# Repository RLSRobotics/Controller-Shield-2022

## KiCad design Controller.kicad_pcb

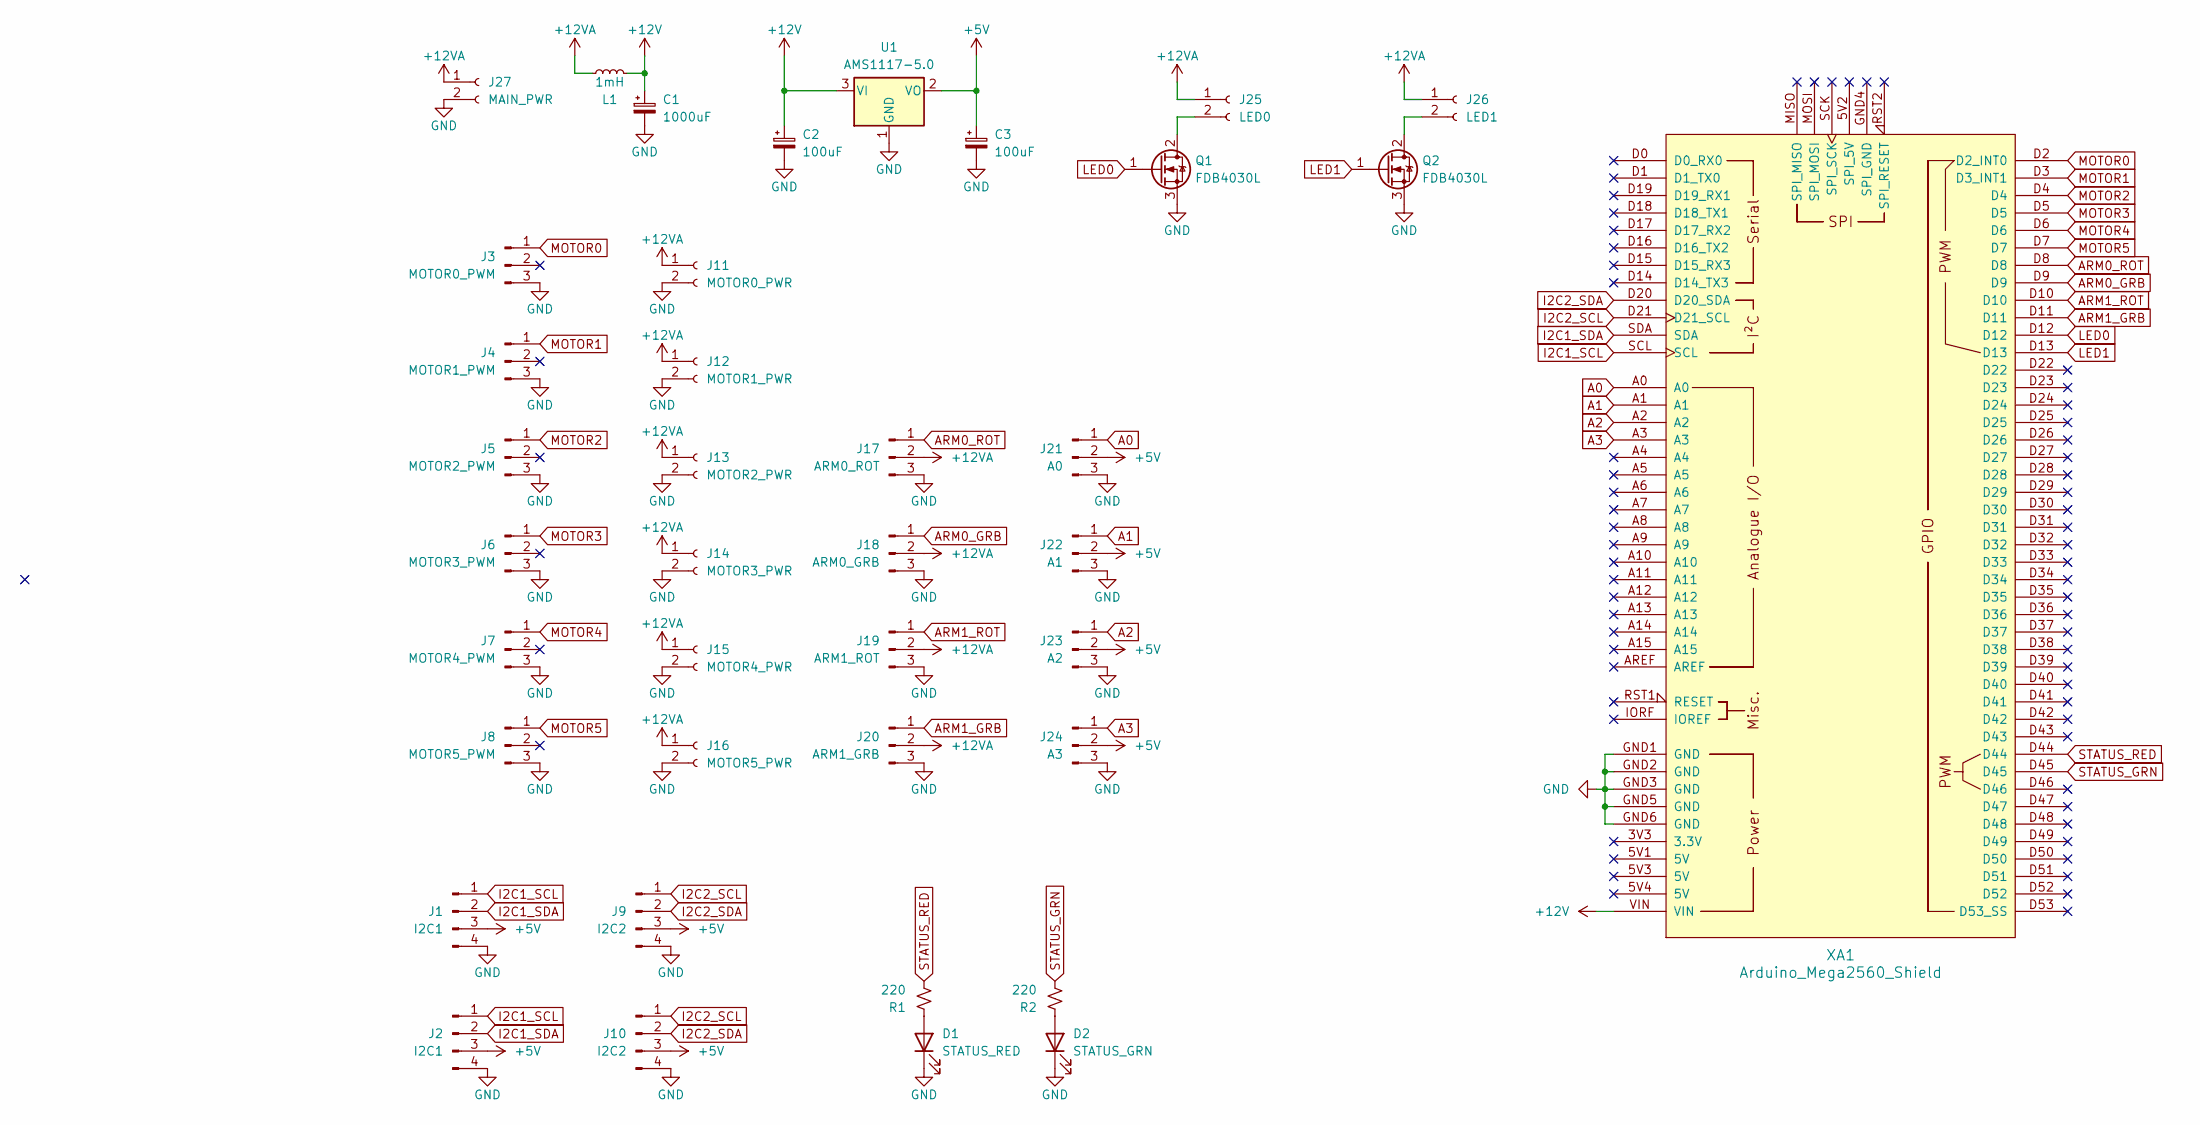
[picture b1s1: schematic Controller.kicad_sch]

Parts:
C1: 1000uF; CP_Radial_D12.5mm_P5.00mm; Part Number UVR1V102MHD
C2, C3: 100uF; CP_Elec_6.3x5.9; Part Number UCW1E101MCL1GS
D1: STATUS_RED; D_0603_1608Metric_Pad1.05x0.95mm_HandSolder
D2: STATUS_GRN; D_0603_1608Metric_Pad1.05x0.95mm_HandSolder
J1, J2: I2C1; PinHeader_1x04_P2.54mm_Horizontal
J3: MOTOR0_PWM; PinHeader_1x03_P2.54mm_Horizontal
J4: MOTOR1_PWM; PinHeader_1x03_P2.54mm_Horizontal
J5: MOTOR2_PWM; PinHeader_1x03_P2.54mm_Horizontal
J6: MOTOR3_PWM; PinHeader_1x03_P2.54mm_Horizontal
J7: MOTOR4_PWM; PinHeader_1x03_P2.54mm_Horizontal
J8: MOTOR5_PWM; PinHeader_1x03_P2.54mm_Horizontal
J9, J10: I2C2; PinHeader_1x04_P2.54mm_Horizontal
J11: MOTOR0_PWR; ESC-PWR
J12: MOTOR1_PWR; ESC-PWR
J13: MOTOR2_PWR; ESC-PWR
J14: MOTOR3_PWR; ESC-PWR
J15: MOTOR4_PWR; ESC-PWR
J16: MOTOR5_PWR; ESC-PWR
J17: ARM0_ROT; PinHeader_1x03_P2.54mm_Horizontal
J18: ARM0_GRB; PinHeader_1x03_P2.54mm_Horizontal
J19: ARM1_ROT; PinHeader_1x03_P2.54mm_Horizontal
J20: ARM1_GRB; PinHeader_1x03_P2.54mm_Horizontal
J21: A0; PinHeader_1x03_P2.54mm_Horizontal
J22: A1; PinHeader_1x03_P2.54mm_Horizontal
J23: A2; PinHeader_1x03_P2.54mm_Horizontal
J24: A3; PinHeader_1x03_P2.54mm_Horizontal
J25: LED0; TerminalBlock_bornier-2_P5.08mm
J26: LED1; TerminalBlock_bornier-2_P5.08mm
J27: MAIN_PWR; ESC-PWR
L1: 1mH; L_Radial_D24.4mm_P23.40mm_Murata_1400series; Part Number 1410516C
Q1, Q2: FDB4030L; TO-263-2
R1, R2: 220; R_0603_1608Metric_Pad0.98x0.95mm_HandSolder
U1: AMS1117-5.0; SOT-223-3_TabPin2
XA1: Arduino_Mega2560_Shield

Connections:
+5V: C3.1, J1.3, J2.3, J9.3, J10.3, J21.2, J22.2, J23.2, J24.2, U1.2 (VO)
+12V: C1.1, C2.1, L1.2, U1.3 (VI), XA1.VIN
+12VA: J11.1, J12.1, J13.1, J14.1, J15.1, J16.1, J17.2, J18.2, J19.2, J20.2, J25.1, J26.1, J27.1, L1.1
A0: J21.1, XA1.A0
A1: J22.1, XA1.A1
A2: J23.1, XA1.A2
A3: J24.1, XA1.A3
ARM0_GRB: J18.1, XA1.D9
ARM0_ROT: J17.1, XA1.D8
ARM1_GRB: J20.1, XA1.D11
ARM1_ROT: J19.1, XA1.D10
GND: C1.2, C2.2, C3.2, D1.1 (K), D2.1 (K), J1.4, J2.4, J3.3, J4.3, J5.3, J6.3, J7.3, J8.3, J9.4, J10.4, J11.2, J12.2, J13.2, J14.2, J15.2, J16.2, J17.3, J18.3, J19.3, J20.3, J21.3, J22.3, J23.3, J24.3, J27.2, Q1.3 (S), Q2.3 (S), U1.1 (GND), XA1.GND1 (GND), XA1.GND2 (GND), XA1.GND3 (GND), XA1.GND5 (GND), XA1.GND6 (GND)
I2C1_SCL: J1.1, J2.1, XA1.SCL
I2C1_SDA: J1.2, J2.2, XA1.SDA
I2C2_SCL: J9.1, J10.1, XA1.D21 (D21_SCL)
I2C2_SDA: J9.2, J10.2, XA1.D20 (D20_SDA)
LED0: Q1.1 (G), XA1.D12
LED1: Q2.1 (G), XA1.D13
MOTOR0: J3.1, XA1.D2 (D2_INT0)
MOTOR1: J4.1, XA1.D3 (D3_INT1)
MOTOR2: J5.1, XA1.D4
MOTOR3: J6.1, XA1.D5
MOTOR4: J7.1, XA1.D6
MOTOR5: J8.1, XA1.D7
unnamed: D2.2 (A), R2.1
unnamed: J25.2, Q1.2 (D)
unnamed: J26.2, Q2.2 (D)
unnamed: D1.2 (A), R1.1
STATUS_GRN: R2.2, XA1.D45
STATUS_RED: R1.2, XA1.D44

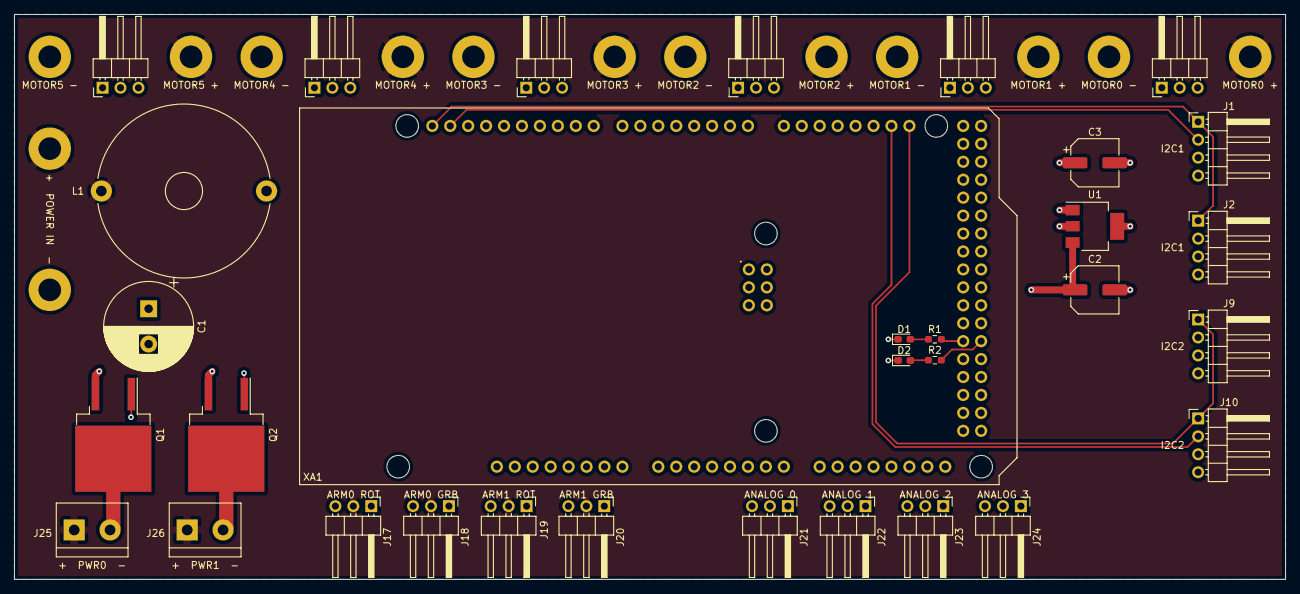
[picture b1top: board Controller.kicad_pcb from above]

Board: 4 copper layers, 180.0 x 80.0 mm, 39 parts (0 on the bottom side), 30 nets.

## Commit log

2022-01-18 Assign pin functions
2022-01-19 Add power supplies & filters
2022-01-20 Add motor connectors
2022-02-02 Add peripheral connectors
2022-02-02 Update power supply
2022-02-15 Complete full schematic
2022-02-15 Add PCB design, minor corrections on schematic
2022-02-18 Switch servos to 12V unfiltered rail
2022-02-18 Decrease board size to 80mm wide
2022-02-18 Add silkscreen labels
2022-02-22 Use 0603 resistors and LED
